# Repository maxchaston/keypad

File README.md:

# Overview
This repo contains PCB designs, firmare and case designs for a variety of keypads designed primarily for the ATMEGA series of MCUs.

Made possible with help from ai03's excellent PCB design resource available at https://wiki.ai03.com/books/pcb-design

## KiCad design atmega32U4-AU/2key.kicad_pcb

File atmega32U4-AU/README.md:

# Overview
Designed for use with the larger "AU" version of the atmega32U4. Uses regular cherry pin pads.

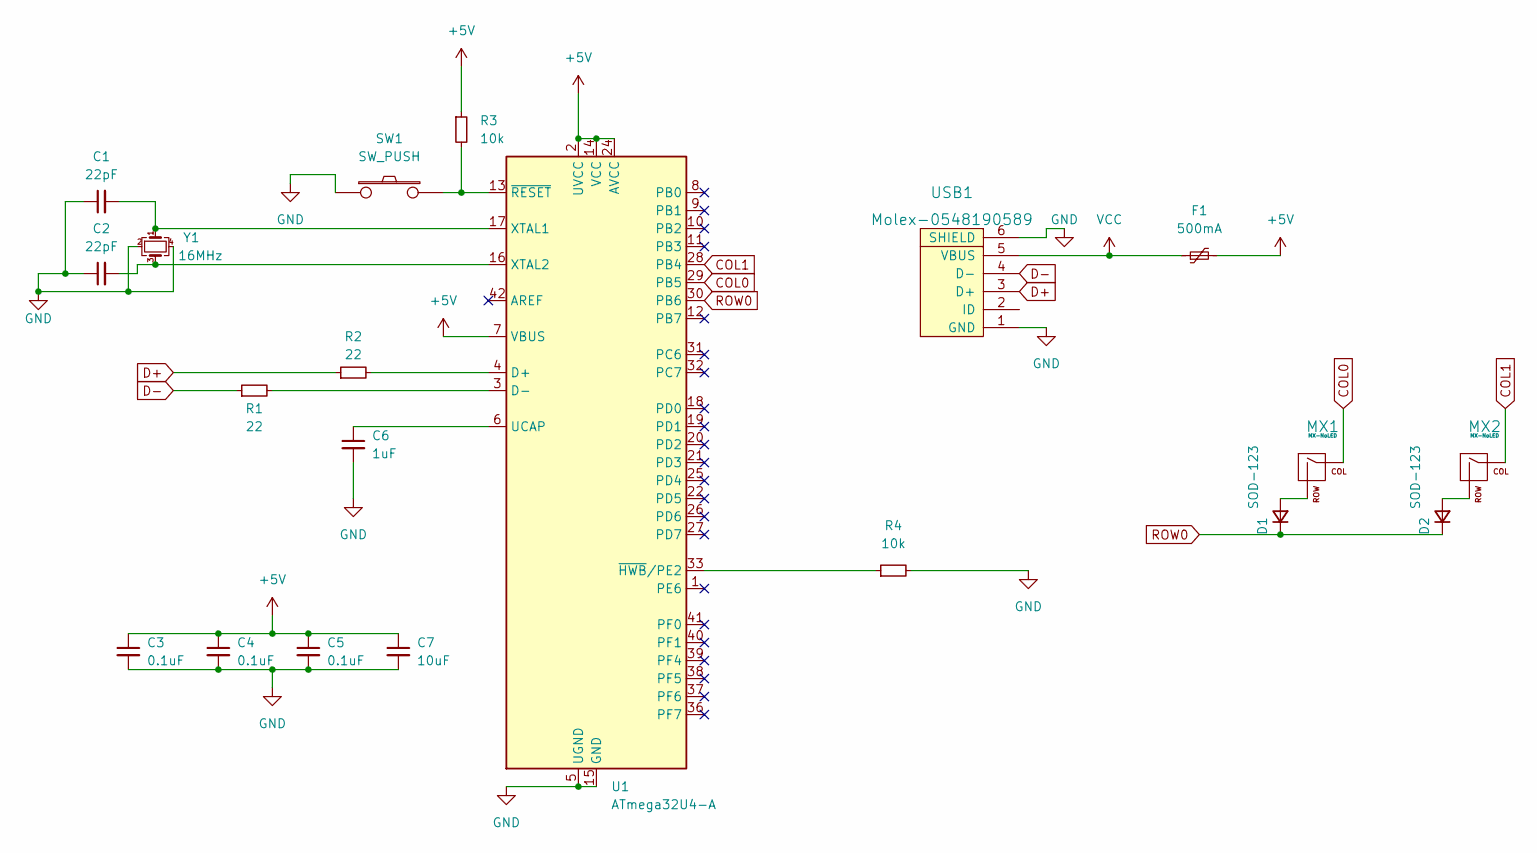
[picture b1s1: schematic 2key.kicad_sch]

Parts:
C1, C2: 22pF; C_0805_2012Metric
C3, C4, C5: 0.1uF; C_0805_2012Metric
C6: 1uF; C_0805_2012Metric
C7: 10uF; C_0805_2012Metric
D1, D2: SOD-123; D_SOD-123
F1: 500mA; Fuse_1206_3216Metric
MX1, MX2: MX-NoLED; MX-1U-NoLED
R1, R2: 22; R_0805_2012Metric
R3, R4: 10k; R_0805_2012Metric
SW1: SW_PUSH; SKQG-1155865
U1: ATmega32U4-A; TQFP-44_10x10mm_P0.8mm
USB1: Molex-0548190589
Y1: 16MHz; Crystal_SMD_3225-4Pin_3.2x2.5mm

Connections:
+5V: C3.1, C4.1, C5.1, C7.1, F1.2, R3.1, U1.2 (UVCC), U1.7 (VBUS), U1.14 (VCC), U1.24 (AVCC), U1.34 (VCC), U1.44 (AVCC)
COL0: MX1.1 (COL), U1.29 (PB5)
COL1: MX2.1 (COL), U1.28 (PB4)
D+: R2.1, USB1.3 (D+)
D-: R1.1, USB1.4 (D-)
GND: C1.1, C2.1, C3.2, C4.2, C5.2, C6.2, C7.2, R4.2, SW1.1, U1.5 (UGND), U1.15 (GND), U1.23 (GND), U1.35 (GND), U1.43 (GND), USB1.1 (GND), USB1.6 (SHIELD), Y1.2, Y1.4
unnamed: C1.2, U1.17 (XTAL1), Y1.1
unnamed: C2.2, U1.16 (XTAL2), Y1.3
unnamed: C6.1, U1.6 (UCAP)
unnamed: D1.2 (A), MX1.2 (ROW)
unnamed: D2.2 (A), MX2.2 (ROW)
unnamed: R1.2, U1.3 (D-)
unnamed: R2.2, U1.4 (D+)
unnamed: R3.2, SW1.2, U1.13 (~RESET)
unnamed: R4.1, U1.33 (~HWB/PE2)
ROW0: D1.1 (K), D2.1 (K), U1.30 (PB6)
VCC: F1.1, USB1.5 (VBUS)

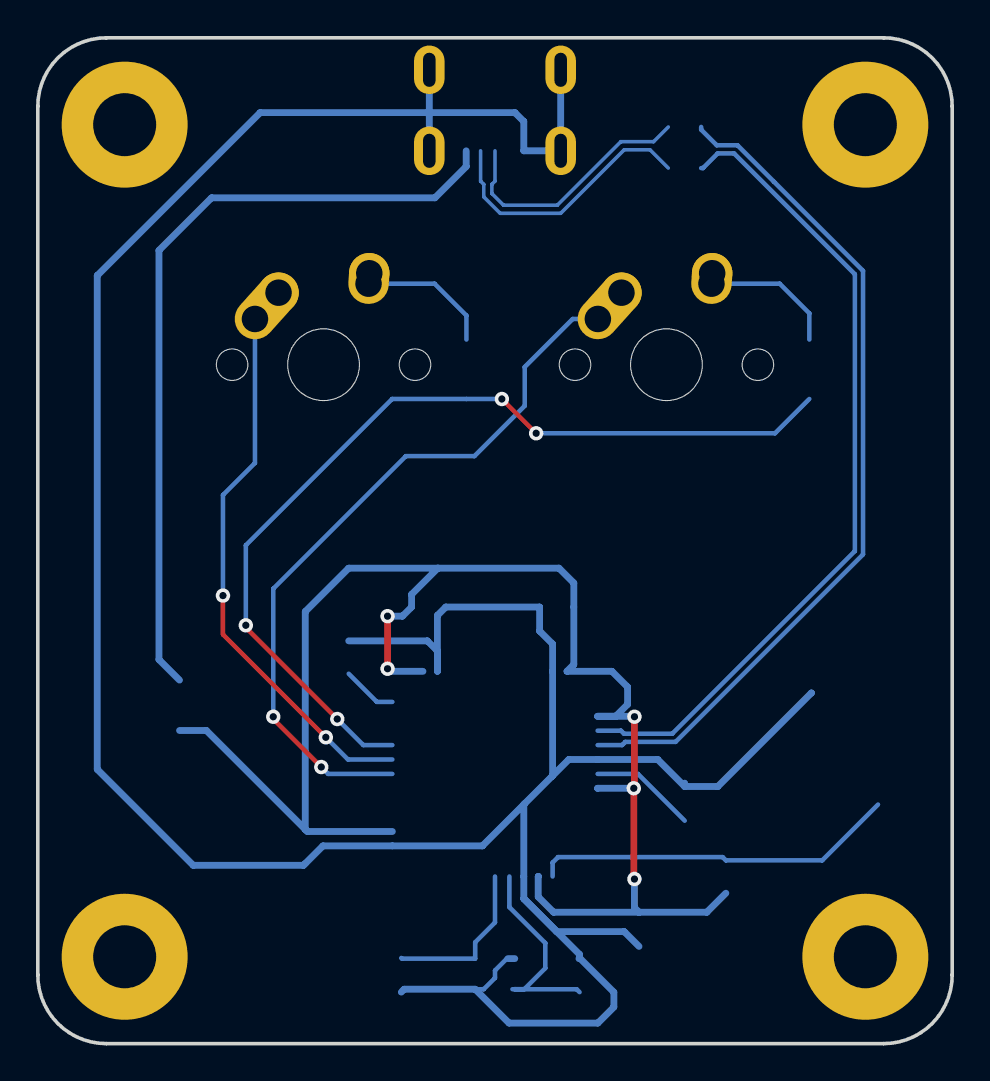
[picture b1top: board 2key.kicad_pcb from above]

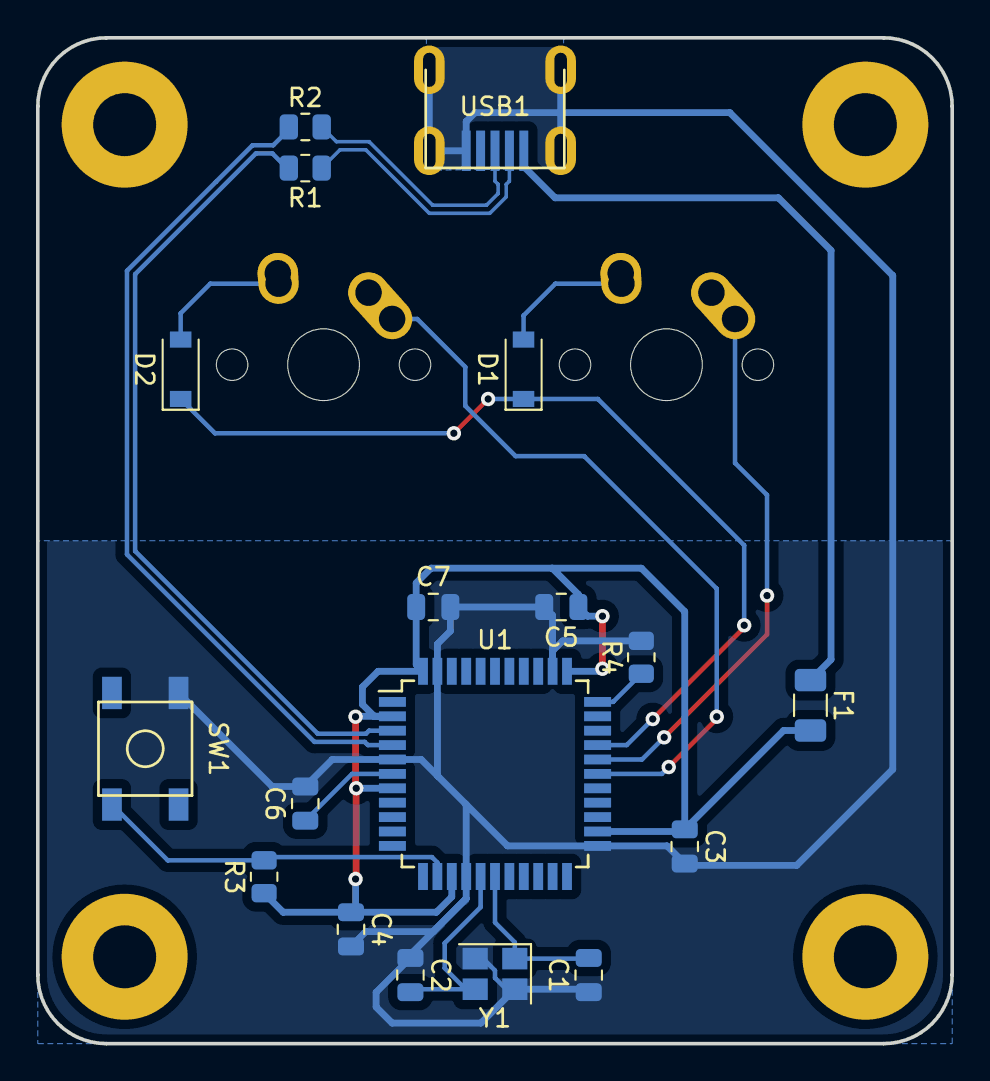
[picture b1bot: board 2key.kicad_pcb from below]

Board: 2 copper layers, 50.8 x 55.9 mm, 20 parts (18 on the bottom side), 17 nets.

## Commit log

2023-01-31 Added render images
2023-01-31 Added top and bottom renders
2023-01-31 Fixed duplicate image
2023-01-31 Update README.md
    Fixed broken relative image path
2023-01-31 Changed directory name
2023-01-31 Added picture
2023-01-31 Update README.md
    Added image to main README
